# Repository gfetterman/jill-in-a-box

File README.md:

# jill-in-a-box
Audio filtering for the Intan EVAL board ADC inputs

The Intan EVAL board ADC accepts 0 to +3.3V inputs. Jill-in-a-box takes audio signals (+/-3.3V), raises their zero to +1.15V, constrains their amplitude to fit between 0 and +3.3V, and applies a 10kHz anti-aliasing filter.

## Version history
* v1.2: anti-aliaising filter passive components changed to use more common components. Filter cutoff is still 10kHz. Specific changes:
  * R25, R26, R27, R28, R29, R30, R31, R32: were 10kOhm, now 39kOhm
  * C14, C18, C19, C21: were 1000pF, now 270pF
  * C13, C17, C20, C22: were 2000pF, now 560pF
* v1.1: added 2-pole Butterworth anti-aliasing filter, cutoff 10kHz, on each channel
* v1.0: first production version

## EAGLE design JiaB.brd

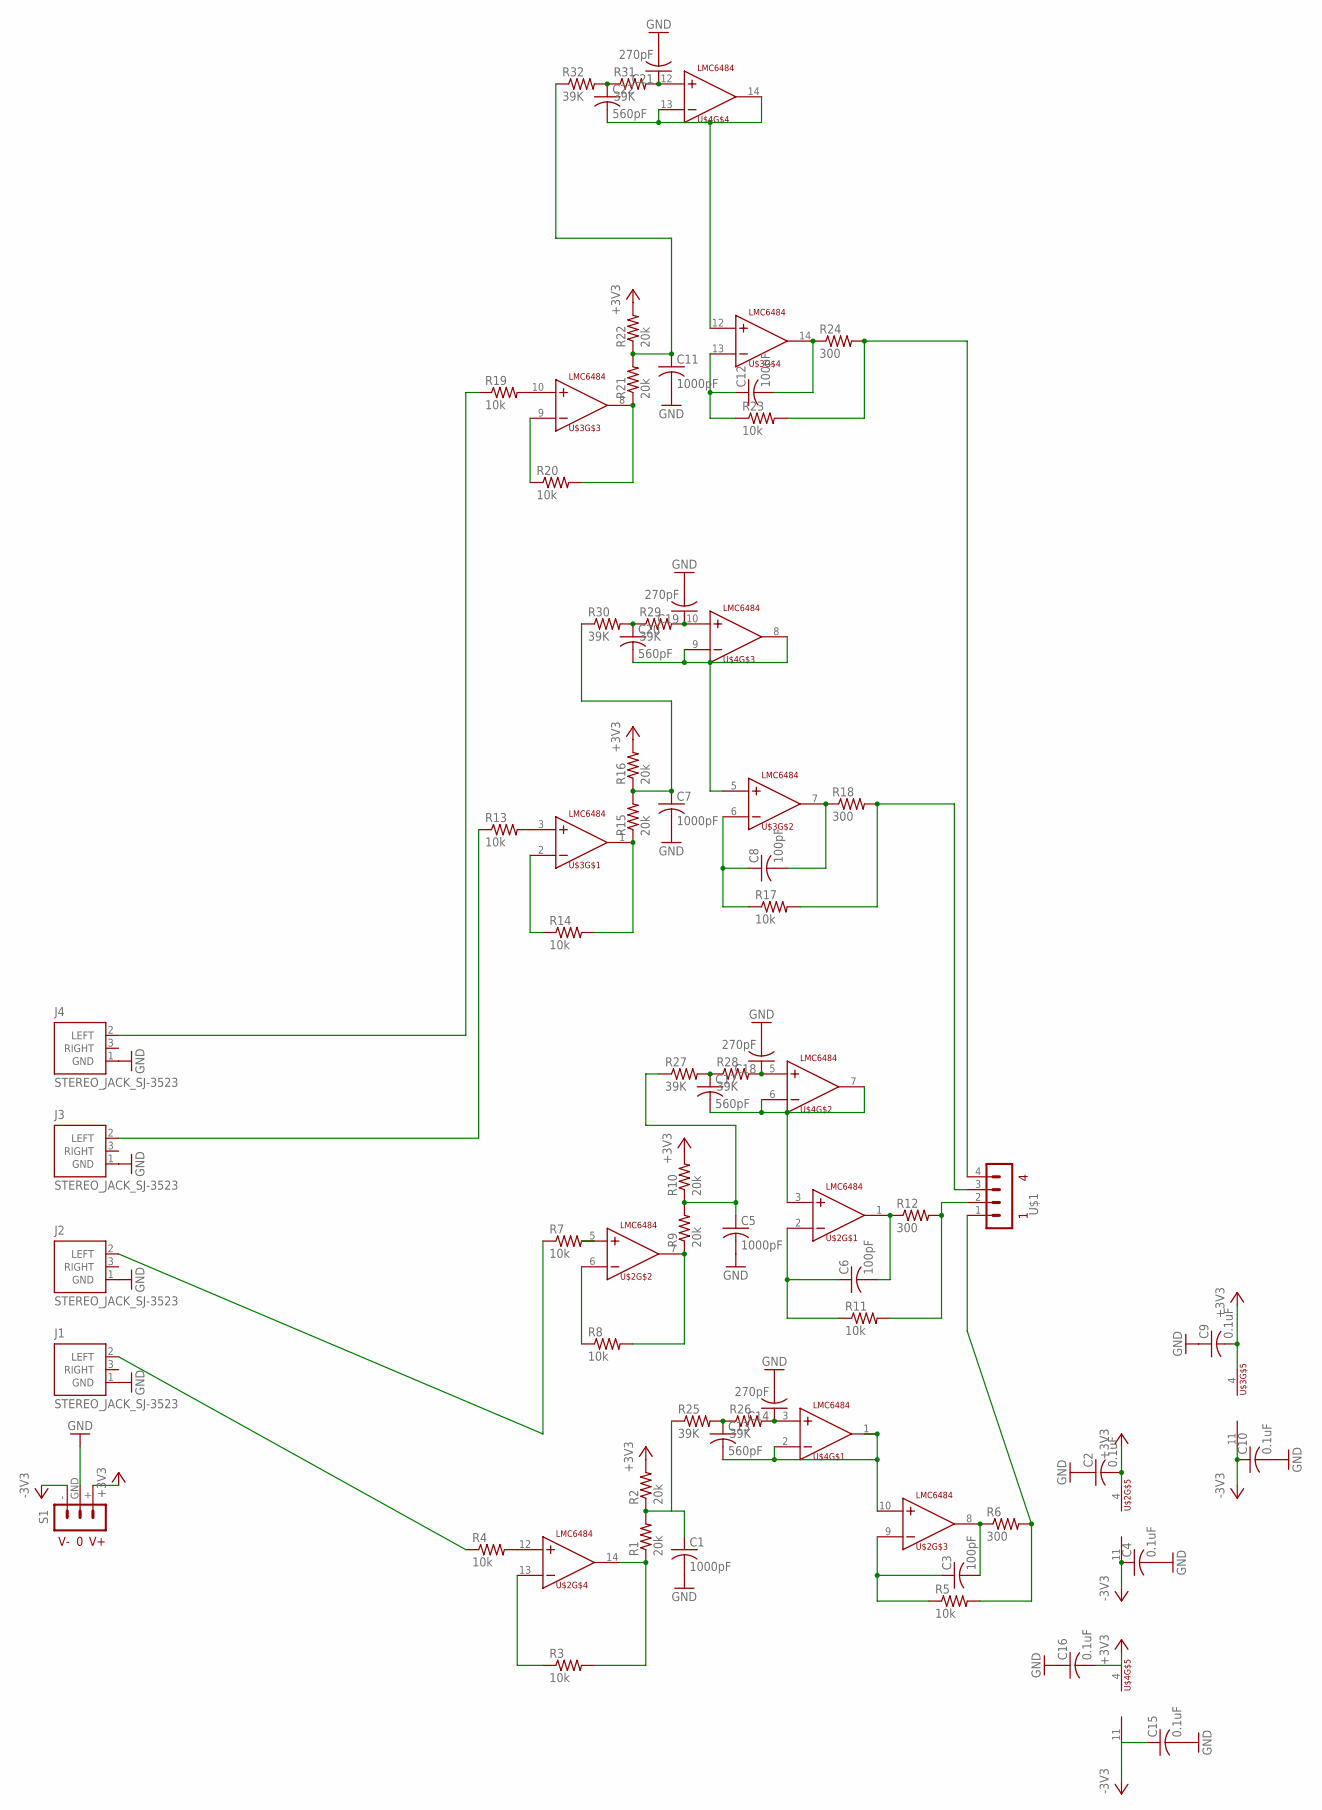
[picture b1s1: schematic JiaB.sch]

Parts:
C1, C5, C7, C11: 1000pF; C025-025X050
C2, C4, C9, C10, C15, C16: 0.1uF; C025-025X050
C3, C6, C8, C12: 100pF; C025-025X050
C13, C17, C20, C22: 560pF; C025-025X050
C14, C18, C19, C21: 270pF; C025-025X050
J1, J2, J3, J4: STEREO_JACK_SJ-3523; SJ-3523
R1, R2, R9, R10, R15, R16, R21, R22: 20k; 0204/7
R3, R4, R5, R7, R8, R11, R13, R14, R17, R19, R20, R23: 10k; 0204/7
R6, R12, R18, R24: 300; 0204/7
R25, R26, R27, R28, R29, R30, R31, R32: 39K; 0204/7
S1: TERMINAL_BLOCK_3_+/-3.3V; TERMINAL_BLOCK_3.5MM_3
U$1: TERMINAL-BLOCK-4
U$2, U$3, U$4: LMC6484; DIL14

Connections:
+3V3: C2.2, C9.2, C16.2, R2.2, R10.2, R16.2, R22.2, S1.+, U$2.4 (VCC+), U$3.4 (VCC+), U$4.4 (VCC+)
-3V3: C4.1, C10.1, C15.1, S1.-, U$2.11 (VCC-), U$3.11 (VCC-), U$4.11 (VCC-)
GND: C1.2, C2.1, C4.2, C5.2, C7.2, C9.1, C10.2, C11.2, C14.2, C15.2, C16.1, C18.2, C19.2, C21.2, J1.1 (GND), J2.1 (GND), J3.1 (GND), J4.1 (GND), S1.GND
unnamed: J1.2 (LEFT), R4.1
unnamed: J2.2 (LEFT), R7.1
unnamed: J3.2 (LEFT), R13.1
unnamed: J4.2 (LEFT), R19.1
unnamed: R1.1, R3.2, U$2.14 (OUT)
unnamed: C1.1, R1.2, R2.1, R25.1
unnamed: R4.2, U$2.12 (IN+)
unnamed: C3.2, R6.1, U$2.8 (OUT)
unnamed: R3.1, U$2.13 (IN-)
unnamed: R7.2, U$2.5 (IN+)
unnamed: R5.2, R6.2, U$1.1
unnamed: R8.2, R9.1, U$2.7 (OUT)
unnamed: C3.1, R5.1, U$2.9 (IN-)
unnamed: C5.1, R9.2, R10.1, R27.1
unnamed: C6.2, R12.1, U$2.1 (OUT)
unnamed: R8.1, U$2.6 (IN-)
unnamed: C6.1, R11.1, U$2.2 (IN-)
unnamed: R11.2, R12.2, U$1.2
unnamed: R13.2, U$3.3 (IN+)
unnamed: R14.2, R15.1, U$3.1 (OUT)
unnamed: C7.1, R15.2, R16.1, R30.1
unnamed: C8.2, R18.1, U$3.7 (OUT)
unnamed: R14.1, U$3.2 (IN-)
unnamed: C8.1, R17.1, U$3.6 (IN-)
unnamed: R17.2, R18.2, U$1.3
unnamed: R19.2, U$3.10 (IN+)
unnamed: R20.2, R21.1, U$3.8 (OUT)
unnamed: C11.1, R21.2, R22.1, R32.1
unnamed: C12.2, R24.1, U$3.14 (OUT)
unnamed: R20.1, U$3.9 (IN-)
unnamed: C12.1, R23.1, U$3.13 (IN-)
unnamed: R23.2, R24.2, U$1.4
unnamed: C14.1, R26.2, U$4.3 (IN+)
unnamed: C13.2, U$2.10 (IN+), U$4.1 (OUT), U$4.2 (IN-)
unnamed: C18.1, R28.2, U$4.5 (IN+)
unnamed: C13.1, R25.2, R26.1
unnamed: C17.1, R27.2, R28.1
unnamed: C17.2, U$2.3 (IN+), U$4.6 (IN-), U$4.7 (OUT)
unnamed: C19.1, R29.2, U$4.10 (IN+)
unnamed: C20.1, R29.1, R30.2
unnamed: C20.2, U$3.5 (IN+), U$4.8 (OUT), U$4.9 (IN-)
unnamed: C21.1, R31.2, U$4.12 (IN+)
unnamed: C22.1, R31.1, R32.2
unnamed: C22.2, U$3.12 (IN+), U$4.13 (IN-), U$4.14 (OUT)

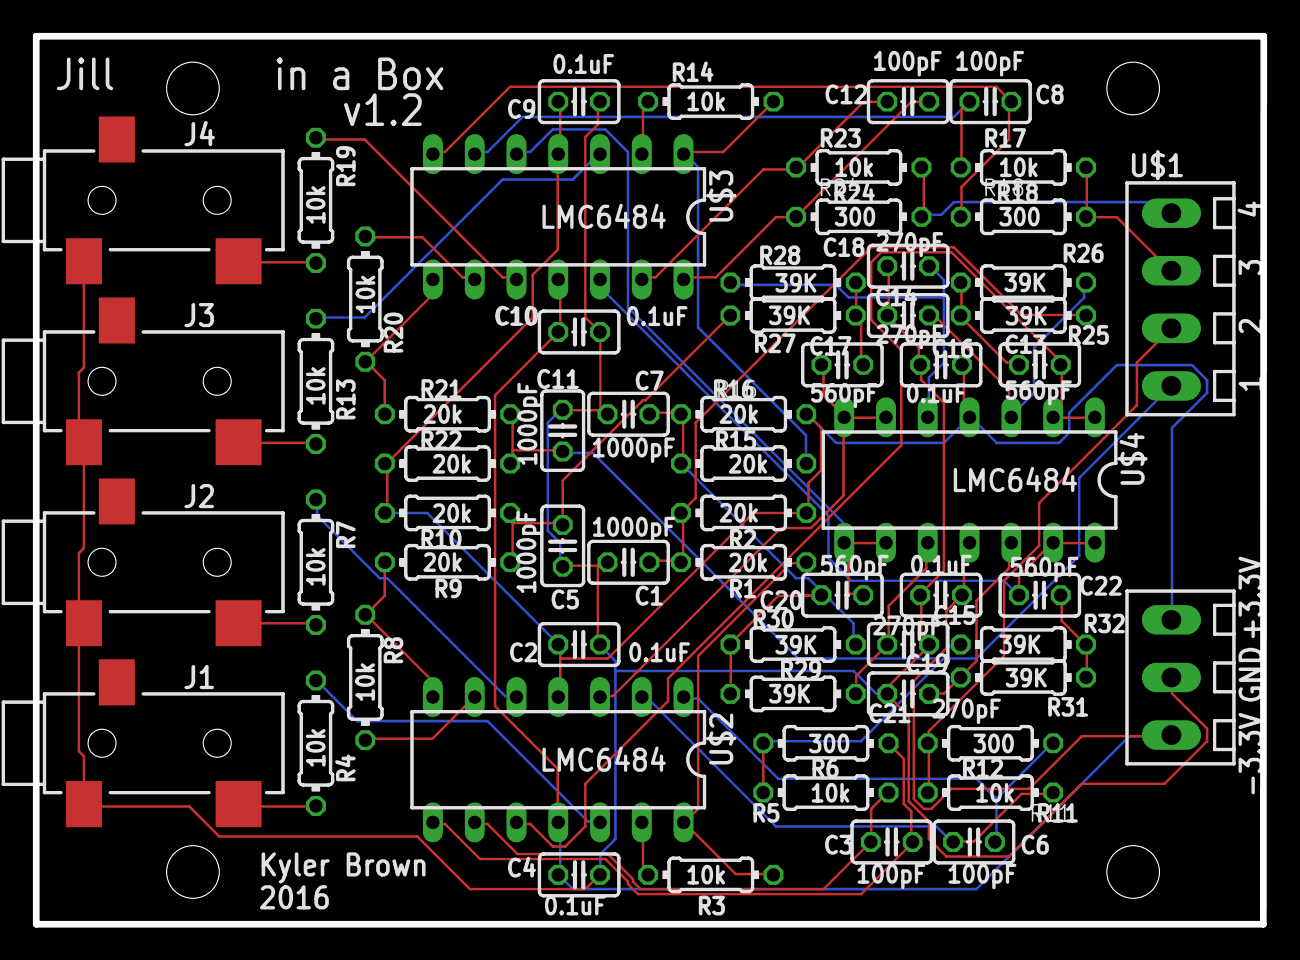
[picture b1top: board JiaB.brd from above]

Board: 2 copper layers, 74.6 x 54.0 mm, 63 parts (0 on the bottom side), 47 nets.

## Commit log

2016-03-17 change anti-alias filter component values
